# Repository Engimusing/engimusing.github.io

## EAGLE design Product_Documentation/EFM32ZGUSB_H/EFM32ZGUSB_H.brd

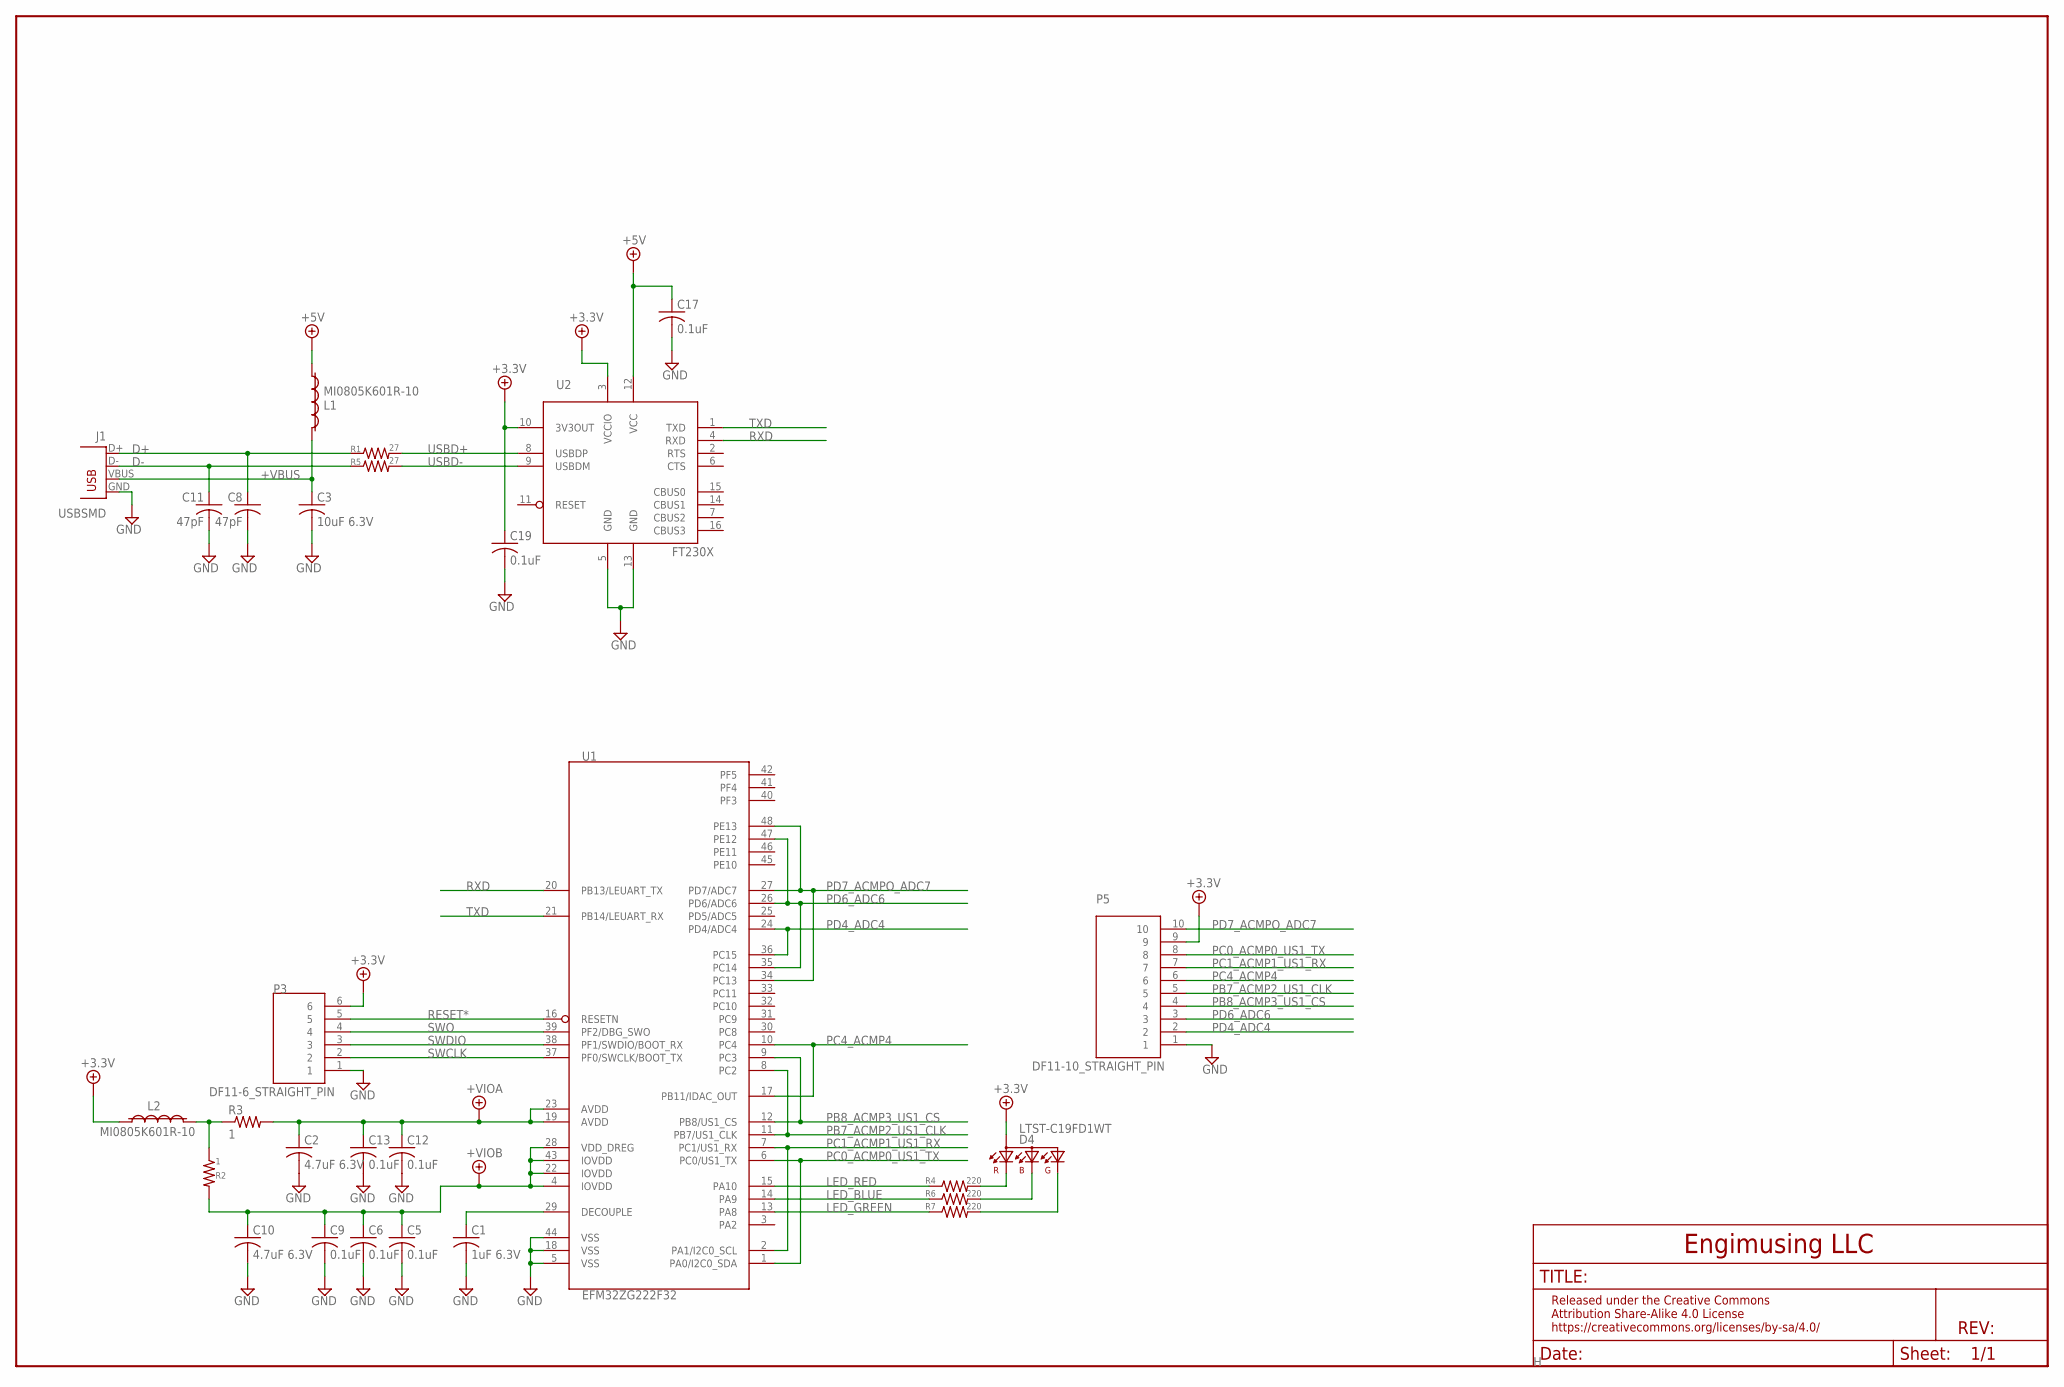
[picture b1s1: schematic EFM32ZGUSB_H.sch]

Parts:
C1: 1uF 6.3V; C0603
C2, C10: 4.7uF 6.3V; C0603
C3: 10uF 6.3V; C0603
C5, C6, C9, C12, C13, C17, C19: 0.1uF; C0402
C8, C11: 47pF; C0603
D4: LTST-C19FD1WT; LED4
J1: USBSMD; USB-MINIB
L1, L2: MI0805K601R-10; L0805_2.5
P3: DF11-6_STRAIGHT_PIN; DF11SP-6-H
P5: DF11-10_STRAIGHT_PIN; DF11SP-10-H
R1, R5: 27; R0603
R2, R3: 1; R0603
R4, R6, R7: 220; R0603
U1: EFM32ZG222F32; QFP48
U2: FT230X; SSOP16

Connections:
+3.3V: C19.1, D4.A4 (A2), L2.1, P3.6, P5.9, U2.3 (VCCIO), U2.10 (3V3OUT)
+5V: C17.1, L1.1, U2.12 (VCC)
+VBUS: C3.1, J1.VBUS, L1.2
+VIOA: C2.1, C12.1, C13.1, R3.2, U1.19 (AVDD), U1.23 (AVDD)
+VIOB: C5.1, C6.1, C9.1, C10.1, R2.2, U1.4 (IOVDD), U1.22 (IOVDD), U1.28 (VDD_DREG), U1.43 (IOVDD)
D+: C8.1, J1.D+, R1.1
D-: C11.1, J1.D-, R5.1
GND: C1.2, C2.2, C3.2, C5.2, C6.2, C8.2, C9.2, C10.2, C11.2, C12.2, C13.2, C17.2, C19.2, J1.GND, P3.1, P5.1, U1.5 (VSS), U1.18 (VSS), U1.44 (VSS), U2.5 (GND), U2.13 (GND)
LED_BLUE: R6.1, U1.14 (PA9)
LED_GREEN: R7.1, U1.13 (PA8)
LED_RED: R4.1, U1.15 (PA10)
unnamed: D4.G3 (CGREEN), R7.2
unnamed: D4.B1 (CBLUE), R6.2
unnamed: C1.1, U1.29 (DECOUPLE)
unnamed: L2.2, R2.1, R3.1
unnamed: D4.R2 (CRED), R4.2
PB7_ACMP2_US1_CLK: P5.5, U1.8 (PC2), U1.11 (PB7/US1_CLK)
PB8_ACMP3_US1_CS: P5.4, U1.9 (PC3), U1.12 (PB8/US1_CS)
PC0_ACMP0_US1_TX: P5.8, U1.1 (PA0/I2C0_SDA), U1.6 (PC0/US1_TX)
PC1_ACMP1_US1_RX: P5.7, U1.2 (PA1/I2C0_SCL), U1.7 (PC1/US1_RX)
PC4_ACMP4: P5.6, U1.10 (PC4), U1.17 (PB11/IDAC_OUT)
PD4_ADC4: P5.2, U1.24 (PD4/ADC4), U1.36 (PC15)
PD6_ADC6: P5.3, U1.26 (PD6/ADC6), U1.35 (PC14), U1.47 (PE12)
PD7_ACMPO_ADC7: P5.10, U1.27 (PD7/ADC7), U1.34 (PC13), U1.48 (PE13)
RESET*: P3.5, U1.16 (RESETN)
RXD: U1.20 (PB13/LEUART_TX), U2.4 (RXD)
SWCLK: P3.2, U1.37 (PF0/SWCLK/BOOT_TX)
SWDIO: P3.3, U1.38 (PF1/SWDIO/BOOT_RX)
SWO: P3.4, U1.39 (PF2/DBG_SWO)
TXD: U1.21 (PB14/LEUART_RX), U2.1 (TXD)
USBD+: R1.2, U2.8 (USBDP)
USBD-: R5.2, U2.9 (USBDM)

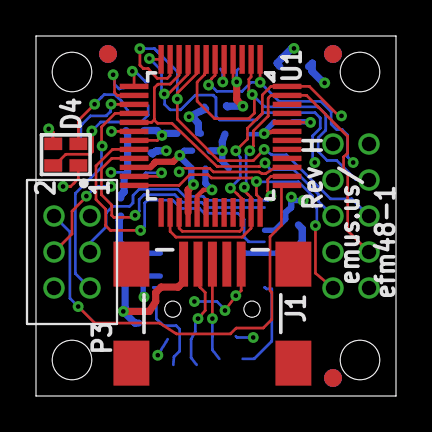
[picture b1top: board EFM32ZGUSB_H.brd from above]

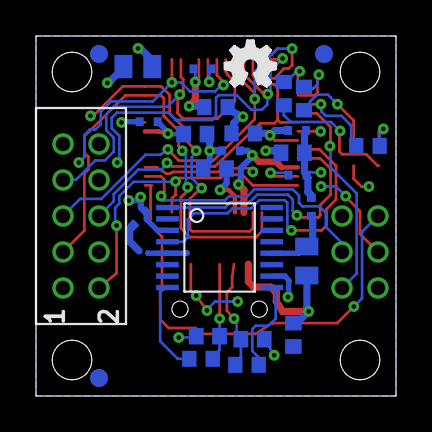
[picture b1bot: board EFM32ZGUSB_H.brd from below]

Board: 4 copper layers, 20.0 x 20.0 mm, 37 parts (29 on the bottom side), 32 nets.

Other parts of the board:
U$1, U$5: LOGO_BULB
U$6: OSHW_FILLX100_NOTEXT
U$10, U$11, U$12, U$13, U$14, U$15: FIDUCIAL_G10

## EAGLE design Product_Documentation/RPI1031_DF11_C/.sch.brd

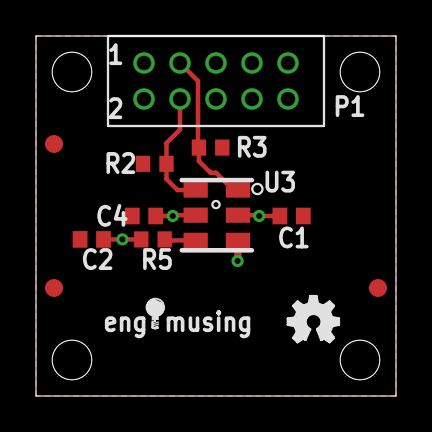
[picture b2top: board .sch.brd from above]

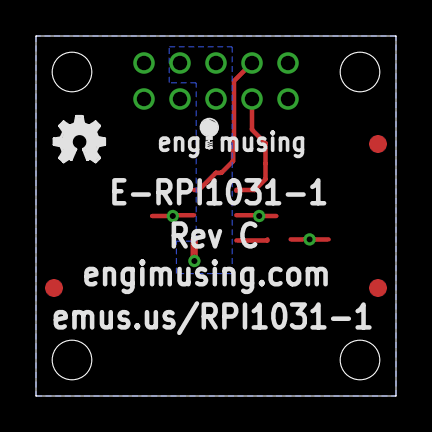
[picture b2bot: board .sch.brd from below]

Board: 2 copper layers, 20.0 x 20.0 mm, 17 parts (2 on the bottom side), 6 nets.

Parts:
C1, C2: 0.1uF; C0603
C4: 1uF 6.3V; C0603
P1: DF11-10_STRAIGHT_PIN; DF11SP-10-H
R2, R3: 20K; R0603
R5: 220; R0603
U3: RPI-1031
U$1, U$5: OSHW_FILLX100_NOTEXT
U$2, U$6: LOGO
U$3: LOGO_BULB
U$4: COPYRIGHT
U$9, U$11, U$12: FIDUCIAL_G10

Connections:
+VIO: C1.1, C2.1, C4.1, P1.9, R5.2, U3.2, U3.5
AN: R5.1, U3.6
DIODE_EN: P1.5, P1.6, P1.7, U3.3
GND: C1.2, C2.2, C4.2, P1.1, R2.1, R3.1
S1: P1.3, R3.2, U3.1
S2: P1.4, R2.2, U3.4

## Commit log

2016-01-14 init
2016-01-14 init2
2016-01-14 Replace master branch with page content via GitHub
2016-01-14 IDE json file
2016-01-15 updated efmusb files
2016-01-15 updated json
2016-01-15 json error 2
2016-01-15 try with just the two essential packages
2016-01-15 crc error - try with just one packages
2016-01-15 crc error - try again
2016-05-11 Use http instead.
    http is simpler and does not mess up with the network where ssl certificates is needed.
    fixes following error for me on linux on a network where custom ssl certificate is needed though
    Error downloading https://engimusing.github.io/arduinoIDE/efm48_1/cortex-m0plus-1.0.1.tar.bz2
    java.lang.RuntimeException: java.lang.Exception: Error downloading https://engimusing.github.io/arduinoIDE/efm48_1/cortex-m0plus-1.0.1.tar.bz2
    at cc.arduino.contributions.packages.ui.ContributionManagerUI.lambda$onInstallPressed$20(ContributionManagerUI.java:176)
    at java.lang.Thread.run(Thread.java:745)
2016-05-11 changed https to http on download file
2016-05-11 Change the download pkg url point to my page.
2016-05-12 update board manager according to latest head 1a0c55c5e2ec80a6f1fa861ccfced8607dfdfca4
2016-05-18 platform.txt: Add program.params.quiet to silent IDE complain
    This is a new option added after IDE 1.6.1
2016-05-21 Move efm_upload to io page & add support of window/linux/mac
2016-06-28 cxfreeze script
    Adding cxfreeze script which is used to create stand alone executable
    versions of the efm_upload.py script
2016-06-29 New version of efm_upload
    Cleaned up efm_upload and wrapped calls in try catch to clean up print
    statements. Also cleaned up print statements in fRead.py and added
    another argument that is just the sketch name. Should cleanly exit in
    all cases I could think of.
2016-06-29 Checking in macosx efm_upload
    Standalone executable version of efm_upload
2016-06-29 Adding the rest of the windows executable files
    Couple of the files were missed because the .gitignore hid them.
2016-06-29 new version of macosx executable for fm_upload
2016-07-08 Fixed efm_upload.py to work with new bootloader
    Fixed efm_upload to work with new bootloader and built new version of
    windows executable
2016-08-10 Fixed linux efm_upload script to use a better bash command.
2016-08-17 added folder for website images
2016-08-17 fix script to work on linux
2016-08-17 added more website files
2016-09-30 Improved the error checking for the efm upload
2016-09-30 More minor improvements to the efm_upload error handling.
2016-09-30 Updated macOX version of fm_upload
2016-12-14 Updated version of EFM_Upload to work with the latest verison of the bootloader
2016-12-14 Updated efm_upload to work with the latest version of the booloader.
2016-12-15 checking in new version of efm_upload for tacos
2016-12-29 Minor update to EFM_Upload so it does not print out the CRC since there is no way to print out a CRC that matches using the bootloader.
2016-12-30 Initial checkin of EFM_Serial2Mqtt. The is a replacement for the EFMComm script.
2016-12-30 Adding Macos version of EFM_Serail2Mqtt
2016-12-30 Added a few more parameters to EFM_Serial2Mqtt
2016-12-30 Modified the efm_upload to check the software device agains the hardware device
2017-01-24 updated firmware and efm_upload to v1.0
2017-01-25 updated v1.0.0
2017-01-25 added 4th parameter to linux version bash script
2017-01-25 updated 1.0 efm_upload
2017-01-25 added sketch and device to efm_upload message
2017-01-25 updated upload files
2017-01-31 added Product_Documentation directory and EFM32ZGUSB docs
2017-01-31 added eagle files for EFM32ZGUSB
2017-01-31 added data sheets for EFM32ZGUSB_H
2017-02-02 Added fcntl lock code to avoid the serial port from being accessed by both EFMcomm and efm_upload
2017-02-02 Few minor changes to make EFM_Serial2Mqtt the same as EFMComm
2017-02-03 Updates to the EFM_Serial2Mqtt script.
    Added better command line argument parsing to EFM_Serial2Mqtt.
    Added a new command line argument for number of retires to
    EFM_Serial2Mqtt. If set to -1 then unlimited retries, it is 0 by
    default.
2017-02-03 Initial versions of cxFreeze for linux and updated versions for windows/osx. Also added scripts for cxfreezing all os's from windows.
2017-02-03 checking in new ubuntu32 version of the built script
2017-02-03 Really adding the new ubuntu32 this time
2017-02-04 Removed some extra files and renamed a script
2017-02-04 Removed the extra macos version
2017-02-04 Checking in os specific tars and a script to build the os specific tars. Also checking in the json file that could be used for these tars.
2017-02-06 Added the 32-bit ARM version of the EFM_Serial2MQTT and a test json file to try out os specific tools tar files.
2017-02-06 minor change to whitespace
2017-02-06 Moved the test file to a new directory and renamed it.
2017-02-06 New versions of the tar fils and the test json file to download them
2017-02-06 Minor change to the test json file.
2017-02-06 Switched to the os independant tools tar files.
2017-02-07 Added linux x64-64 unique version to the json file, added arm64 built version of Serial2Mqtt
2017-02-07 Adding new package for ARM32 bit.
2017-02-07 Fixed the eol characters on the scripts.
2017-02-07 Added back in some .py files that were actually needed.
2017-02-09 updated firmware
2017-02-09 updated checksum and size
2017-02-09 fix error
2017-02-09 another fix
2017-02-09 New version of the efm_upload that is better at handling the case where the board is spewing text.
2017-02-09 New versions of the tools which includes a new version better version of efm_upload. Also fixed the eol for efm_upload.py
2017-02-15 added logo
2017-02-15 install scripts
2017-02-16 Initial hosting of openhab-2.0.0.zip
2017-02-16 added 99-serial2mqtt.rules file
2017-02-16 fixed download command error
2017-02-16 fixed download command error #2
2017-02-16 fixed bug in rules file
2017-02-16 99-serial2mqtt again
2017-02-16 added serial2mqtt.py to install dir
2017-02-16 added init scripts for serial2mqtt
2017-02-17 fixed init scripts again
2017-02-17 set up for logging
2017-02-17 logging 2
2017-02-17 logging 3
2017-02-22 took newgrp out of script
2017-03-02 Initial upload of Engimusing Tools Setup.
2017-03-03 Updated installer to include EFM_Serial2Mqtt script and setup shortcuts to the script. Added script for setting up the inputs to Serial2Mqtt
2017-03-03 Added a ton of comments to the installer script and fixed a minor issue with how the environment variables were set
2017-03-03 Inno setup is bad a saving the file. Here is the abosulte latest mostly just more comments
2017-03-10 update for efm32-1.0.1 #2
2017-03-10 update for efm32-1.0.1 #3
2017-03-10 update for efm32-1.0.1 #4
2017-03-10 update for efm32-1.0.1 #5
2017-03-10 update for efm32-1.0.1 #6
2017-03-10 update for efm32-1.0.1 #7
2017-03-13 update for efm32-1.0.1 #8
2017-03-13 removed caption from schematic
2017-03-14 added HTU21D documentation
2017-03-14 added HTU21D documentation 2
2017-03-14 Added HTU21D_DF11_B documentation
2017-03-15 added TMP102 documentation
2017-03-15 renamed files
2017-03-15 fixed file name
2017-03-15 Added MQ7 docs
2017-03-15 mq7 data sheet
2017-03-15 added relay data sheet
2017-03-15 file rename
2017-03-15 added tg110 datasheet and manual
2017-03-16 Fixed a typo in the installer for setting up the desktop icons.
2017-03-16 Adding TMP_DF11_MQTT example configuration.
2017-03-21 added schematics, board files, and data sheets
2017-03-21 fixed broken links
2017-04-03 Initial commit of example generation tool.
2017-04-03 Fixed a typo in the configuration folder name.
2017-04-04 Checked in a bunch of new configuraiton files. There is now a configuration file for all devices that have device classes.
2017-04-04 Minor formatting changes.
2017-04-05 fixed bug in template & enabled RS232x2 for ACS716
2017-04-06 Configuration file for MLX92212
2017-04-06 Minor formatting change
2017-04-07 Moved the variable setup into it's own file.
2017-04-07 Configuration file for the DualCT101530
2017-04-07 Added ignore for generated examples so they will not be checked in by accident. Just checkout and run generateExamples.py if you need them
2017-04-07 Adding new DualQRE113 configuration and support to the templates for multiple device example generation
2017-04-10 Minor change to CT101530 configuration to use 2 devices instead of a single dual device.
2017-04-10 Adding configuration for the RPI1031 tilt sensor
2017-04-12 added paho.mqtt.python and odroid installer
2017-04-14 updated odroid installer and serial2mqtt
2017-04-20 added ADXL362 DF11 examples
2017-04-20 added config for SSC pressure sensor
2017-05-25 Added configuration for Cap Sense Example code
2017-06-01 updated templates to fix minor errors and add the Toggle class
2017-06-01 Moved example templates into a sub directory and moved the buildAllExamples script from the firware repo into the new tools directory too.
2017-06-01 Updated git ignore file. switched to env variables for all the paths in the build all examples script.
2017-06-01 removed the only generated example that was checked in
2017-06-01 Added summary log for listing the results of all the built examples.
2017-06-01 Added Device printer objects to the templates.
2017-06-07 Updated templates for the example generater to use the TogglePin class.
2017-06-11 efm32-1.0.2 update #1
2017-07-01 Checking in the ESP8266 flash download tool version 3.4.8 and the 1.5.4 AiThinker ESP8266 firmare
2017-09-20 Added MQ7 DF11 board to code generation configuration
2017-09-23 Added SerialParser section to the example generator for a section for parsing the serial ports. Also Added CPC1002 example
2017-09-27 Added support for Additional MQTT commands in the comments for a device.
2017-09-30 Checked in the scripts and cfg files for doxygen
2017-12-15 added daemon installer
2018-01-28 added website tutorial files
2018-01-28 updated website tutorial filenames
2018-02-10 Added the new serial handshake to the efm_upload. It should now work with the most recent bootloader and the older bootloader as well.
2018-02-17 Latest version of the efm source and tools.
2018-02-17 checking in new test json file
2018-02-17 Fixed EOL
2018-02-17 another test
2018-02-17 Strangeness on the :
2018-02-17 added in a missing comma
2018-02-17 Minor fix to how the tar file was orginized.
2018-02-17 Turned off the build tools option and added an explaination file for how to use the scripts.
2018-03-15 moved tutorial files
2018-03-22 Updating engimusing json file so the latest version of the tools and libraries are available to customers.
2018-10-05 Updated example templates and configuration to no longer use the printer objects.
2018-11-11 Uploading latest version of engimusing library
2018-11-29 added force to rm and mv commands to avoid typing y thousands of times

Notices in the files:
Product_Documentation/EFM32ZGUSB_H/EFM32ZGUSB_H.brd:
Released under the Creative Commons Attribution Share-Alike 4.0 License
https://creativecommons.org/licenses/by-sa/3.0
parts and their libraries:
Engimusing: Released under the Creative Commons
Attribution Share-Alike 4.0 License
https://creativecommons.org/licenses/by-sa/4.0
